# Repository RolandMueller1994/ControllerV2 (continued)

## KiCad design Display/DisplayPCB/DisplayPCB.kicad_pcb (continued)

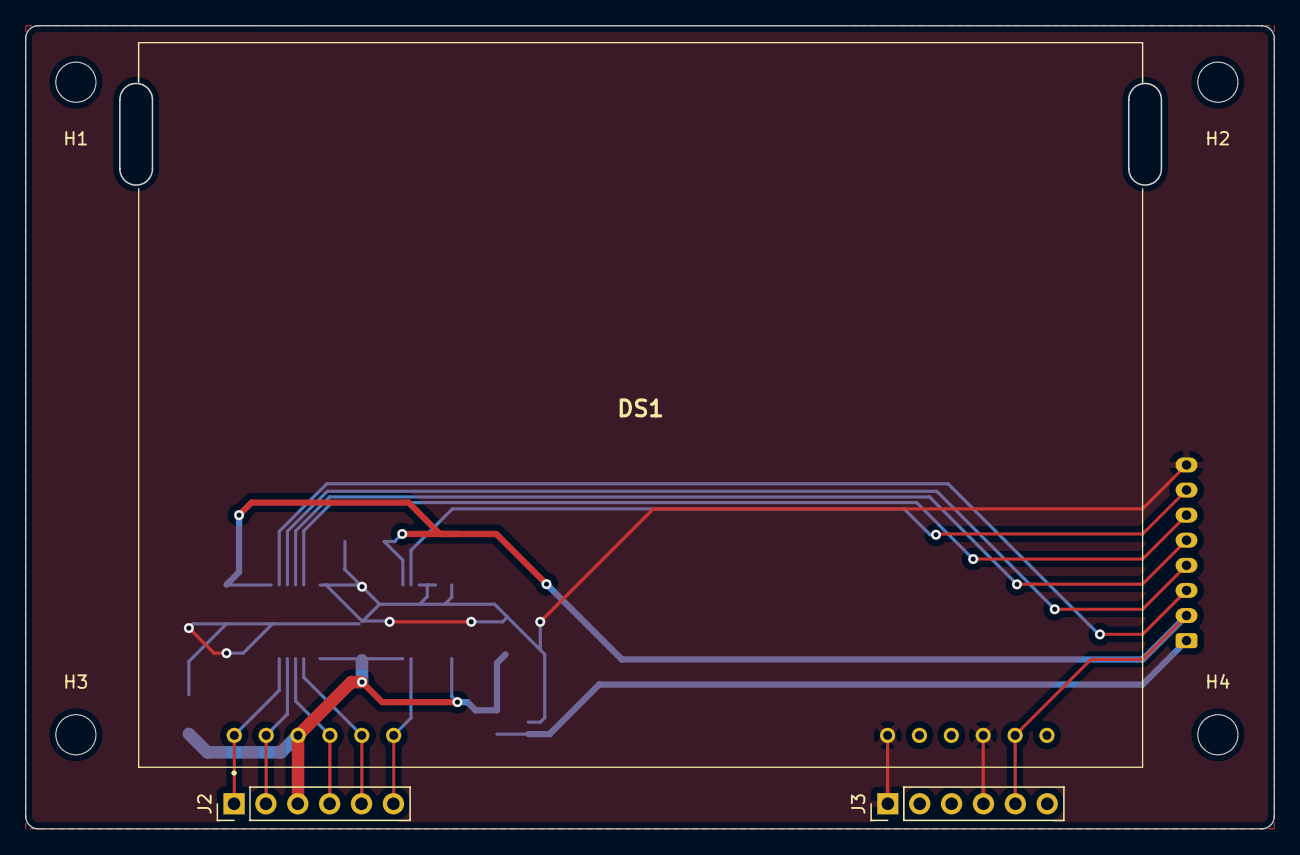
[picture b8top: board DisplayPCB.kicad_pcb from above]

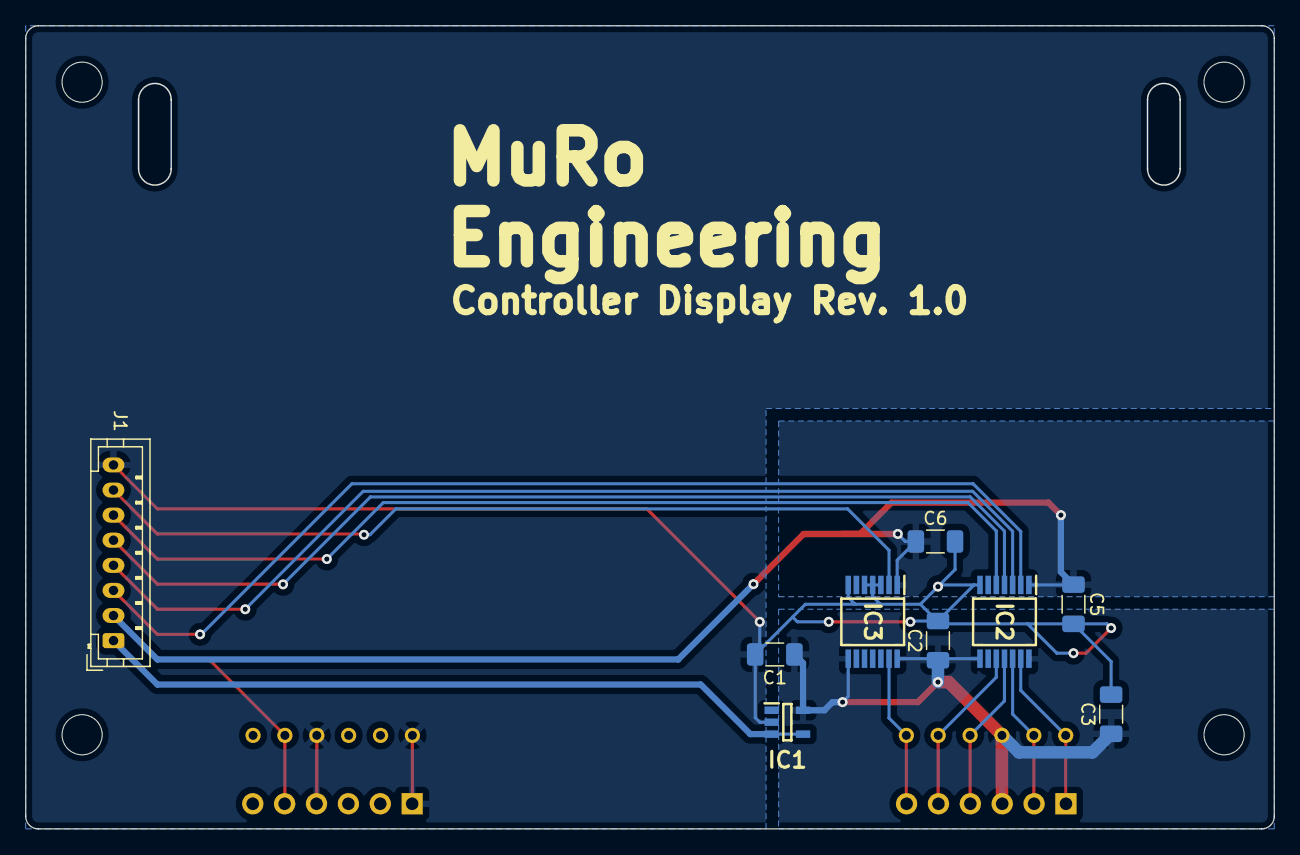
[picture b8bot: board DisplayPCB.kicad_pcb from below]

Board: 2 copper layers, 99.5 x 64.0 mm, 16 parts (9 on the bottom side), 14 nets.

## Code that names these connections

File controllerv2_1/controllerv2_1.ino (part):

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#define REF_GREEN 7
#define REF_STATUS 8

#define I2C_RESET 12

#define EN_MATRIX 33
#define OE_MATRIX 34
#define SER_MATRIX 35
#define SRCLK_MATRIX 36
#define SRCLR_MATRIX 37
#define RCLK_MATRIX 38

#define OE_LOWER 13
#define SER_LOWER 31
#define SRCLK_LOWER 30
#define SRCLR_LOWER 29
#define RCLK_LOWER 28

#define OE_UPPER 43
#define SER_UPPER 47
#define SRCLK_UPPER 46
#define SRCLR_UPPER 45
#define RCLK_UPPER 44


ShiftRegister74HC595<10> regMatrix(SER_MATRIX, SRCLK_MATRIX, RCLK_MATRIX);
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Adafruit_MCP23X08 mcp_status2;
Adafruit_MCP23X08 mcp_status3;

#define INT_MATRIX 32
#define INT_STATUS 42

#include "linkedList.h"

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}

void setupMCP() {
  pinMode(INT_MATRIX, INPUT);
  pinMode(INT_STATUS, INPUT);

  if(!mcp_matrix1.begin_I2C(0x20))
    SerialMuted("Matrix 1 offline\n");
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  pinMode(SRCLR_MATRIX, OUTPUT);
  digitalWrite(SRCLR_MATRIX, LOW);

  pinMode(OE_LOWER, OUTPUT);
  digitalWrite(OE_LOWER, HIGH);
  pinMode(SRCLR_LOWER, OUTPUT);
  digitalWrite(SRCLR_LOWER, LOW);

  pinMode(OE_UPPER, OUTPUT);
  digitalWrite(OE_UPPER, HIGH);
  pinMode(SRCLR_UPPER, OUTPUT);
  digitalWrite(SRCLR_UPPER, LOW);

  pinMode(I2C_RESET, OUTPUT);
  digitalWrite(I2C_RESET, LOW);
  delay(1000);
  digitalWrite(I2C_RESET, HIGH);
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    midiInst.turnThruOff();
  display();
  delay(5000);
  //attachInterrupt(digitalPinToInterrupt(INT_MATRIX), matrixIsr, FALLING);
  readLoopConn();
  //displayPage = mainDisplay;
  readBank();
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
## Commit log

2022-10-18 Inital commit
2022-10-19 Fixed interrupt logic
2022-11-27 Left and right loop order change
2022-11-27 Loop order done
2022-11-27 Fixed loop move
2022-11-27 Loop order fixed and tested, run display with loop order, reset changed for stereo loops, stereo loop change fixed
2022-11-28 Loop order display centered
2022-11-28 Brightness control
2022-11-29 Added copy preset and bank functionality
2022-12-03 First audio path activate. Parallel and phase reverse already implements
2022-12-08 Added faceplate
2022-12-08 Faceplate page size
2022-12-08 Flipped version for drill
2022-12-08 Fixed wrong menu transistion due to array point overflow
2022-12-17 Modified MCP lib. Control leds working
2022-12-18 Changed switch pcb left to 9V led supply
2022-12-18 Added 9V supply on PSU for LEDs on switch. Changed FRAM supply
2022-12-18 Changed FRAM pinout, 9V center negative
2022-12-29 Added libs
2023-01-02 Added library
2023-01-02 Added gitignore
2023-01-02 Changed paths for linux
2023-01-02 Cleanup
2023-01-02 Changed library paths to relative
2023-01-03 Main mostly wired. Push for replacement
2023-01-03 Mixer, controll and supply wiring done. Matrix connections missing
2023-01-03 DRC clean PCB
2023-01-03 Added jacks library
2023-01-03 Fixed library imports
2023-01-03 Changed PSU_Processor PCB to adapt changes on Main PCB
2023-01-05 Fixed library imports. Changed psu pcb
2023-01-05 Added pin header for matrix test
2023-01-08 3D models and fixed pcbs
2023-01-20 Multiple enclosure versions
2023-02-04 Commit for branch change
2023-02-05 Changed main to 8 loop version. Might add buffers later
2023-02-05 Changed switch left to 3 switches
2023-02-05 Changed Enclosure bottom for 8 loops
2023-02-05 Enclosure changed for 8 loops
2023-02-05 Added radius to corners
2023-02-12 Enclosure and faceplate for 8 loops
2023-03-26 Added amp schematic
2023-03-26 Layout of PGAs
2023-03-26 Added chip select for amps on main pcb
2023-03-26 Main schematic was not saved
2023-03-27 Added schematic pdfs
2023-10-08 Commit before change to Nano
2023-10-08 New switch pcb version with IO expander
2023-11-19 New version with smaller enclosure
2023-11-19 New version with connection bending
2023-11-19 Backup
2023-11-19 Added holes for fasteners
2023-11-19 All drill holes added
